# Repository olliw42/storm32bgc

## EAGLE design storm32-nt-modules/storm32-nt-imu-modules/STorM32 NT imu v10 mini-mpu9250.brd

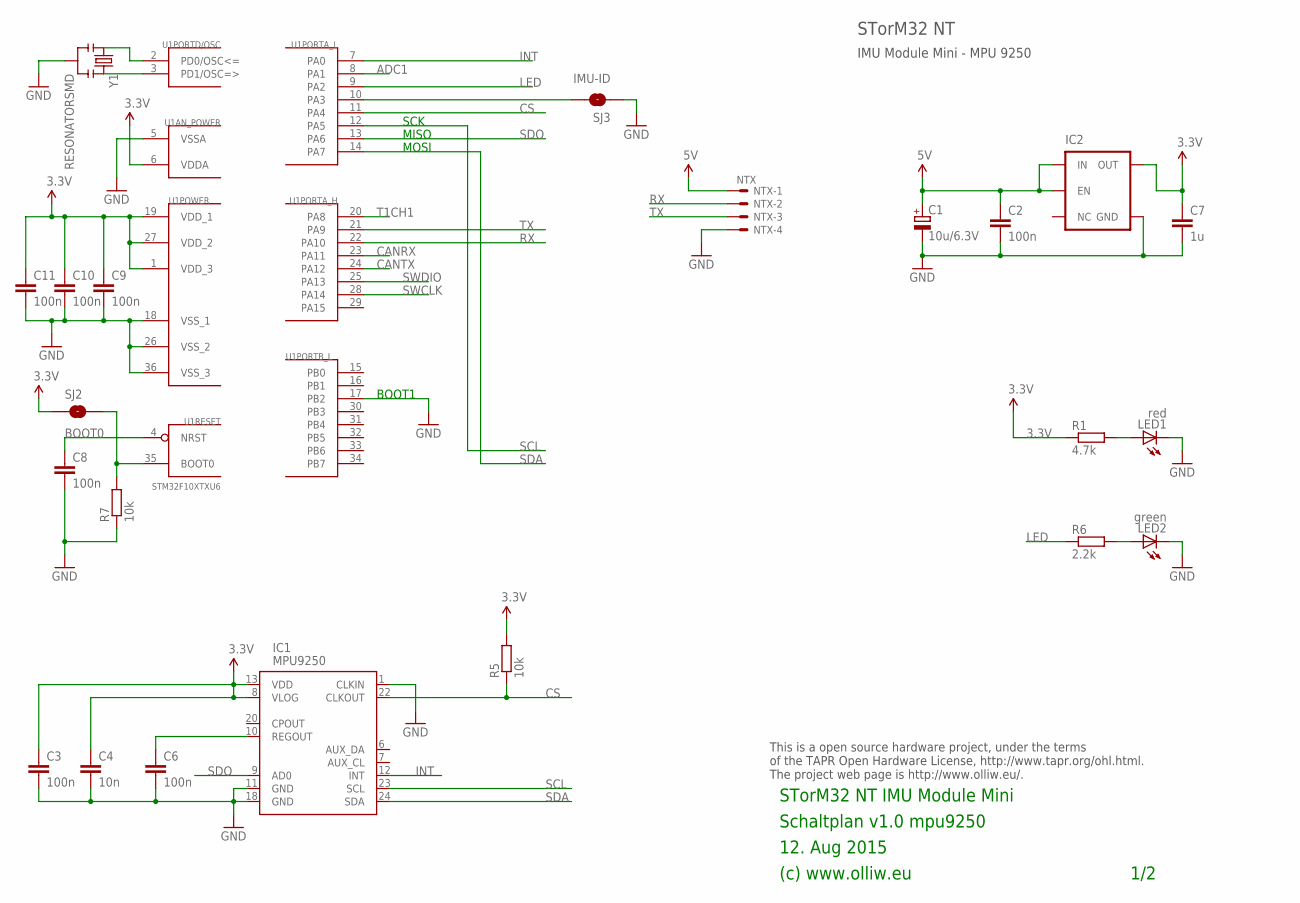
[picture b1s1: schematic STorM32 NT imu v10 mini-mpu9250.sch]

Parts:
C1: 10u/6.3V; SMC_A
C2, C3, C6, C8, C9, C10, C11: 100n; C0402
C4: 10n; C0402
C7: 1u; C0402
IC1: MPU9250; QFN-24-3X3
IC2: V_REG_TPS76433SOT23-5; SOT23-5
LED1: red; CHIPLED_0603
LED2: green; CHIPLED_0603
NTX: NTX; SM04B-SRSS-TB
R1: 4.7k; R0402
R5, R7: 10k; R0402
R6: 2.2k; R0402
SJ2: BOOT0; SJ_2S-NO
SJ3: IMU-ID; SJ_2S-NO
U1: STM32F10XTXU6; VFQFPN36
Y1: RESONATORSMD; RESONATOR-SMD

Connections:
3.3V: C3.1, C4.1, C7.1, C9.1, C10.1, C11.1, IC1.8 (VLOG), IC1.13 (VDD), IC2.5 (OUT), R1.1, R5.2, SJ2.1, U1.1 (VDD_3), U1.6 (VDDA), U1.19 (VDD_1), U1.27 (VDD_2)
5V: C1.+, C2.1, IC2.1 (IN), IC2.3 (EN), NTX.1
ADC1: U1.8 (PA1)
CANRX: U1.23 (PA11)
CANTX: U1.24 (PA12)
CS: IC1.22 (CLKOUT), R5.1, U1.11 (PA4)
GND: C1.-, C2.2, C3.2, C4.2, C6.2, C7.2, C8.2, C9.2, C10.2, C11.2, IC1.1 (CLKIN), IC1.11 (GND), IC1.18 (GND), IC2.2 (GND), LED1.C, LED2.C, NTX.4, R7.1, SJ3.1, U1.5 (VSSA), U1.17 (PB2), U1.18 (VSS_1), U1.26 (VSS_2), U1.36 (VSS_3), Y1.2
INT: IC1.12 (INT), U1.7 (PA0)
LED: R6.1, U1.9 (PA2)
unnamed: C8.1, U1.4 (NRST)
unnamed: LED2.A, R6.2
unnamed: R7.2, SJ2.2, U1.35 (BOOT0)
unnamed: U1.2 (PD0/OSC<=), Y1.1
unnamed: U1.3 (PD1/OSC=>), Y1.3
unnamed: LED1.A, R1.2
unnamed: C6.1, IC1.10 (REGOUT)
RX: NTX.2, U1.22 (PA10)
RX2: SJ3.2, U1.10 (PA3)
SCL: IC1.23 (SCL), U1.12 (PA5)
SDA: IC1.24 (SDA), U1.14 (PA7)
SDO: IC1.9 (AD0), U1.13 (PA6)
SWCLK: U1.28 (PA14)
SWDIO: U1.25 (PA13)
T1CH1: U1.20 (PA8)
TX: NTX.3, U1.21 (PA9)

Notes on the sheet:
12. Aug 2015
(c) www.olliw.eu
STorM32 NT IMU Module Mini
Schaltplan v1.0 mpu9250
This is a open source hardware project, under the terms of the TAPR Open Hardware License, http://www.tapr.org/ohl.html. The project web page is http://www.olliw.eu/.
1/2
IMU Module Mini - MPU 9250
STorM32 NT
SCK
MISO
MOSI
BOOT1

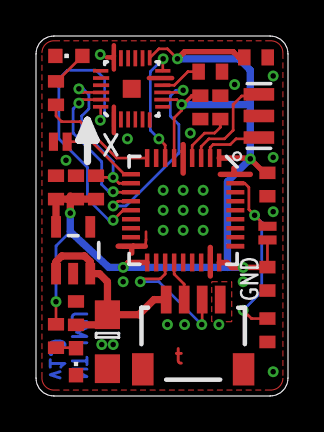
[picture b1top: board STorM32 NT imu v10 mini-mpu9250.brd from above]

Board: 2 copper layers, 14.0 x 20.0 mm, 23 parts (0 on the bottom side), 19 nets.

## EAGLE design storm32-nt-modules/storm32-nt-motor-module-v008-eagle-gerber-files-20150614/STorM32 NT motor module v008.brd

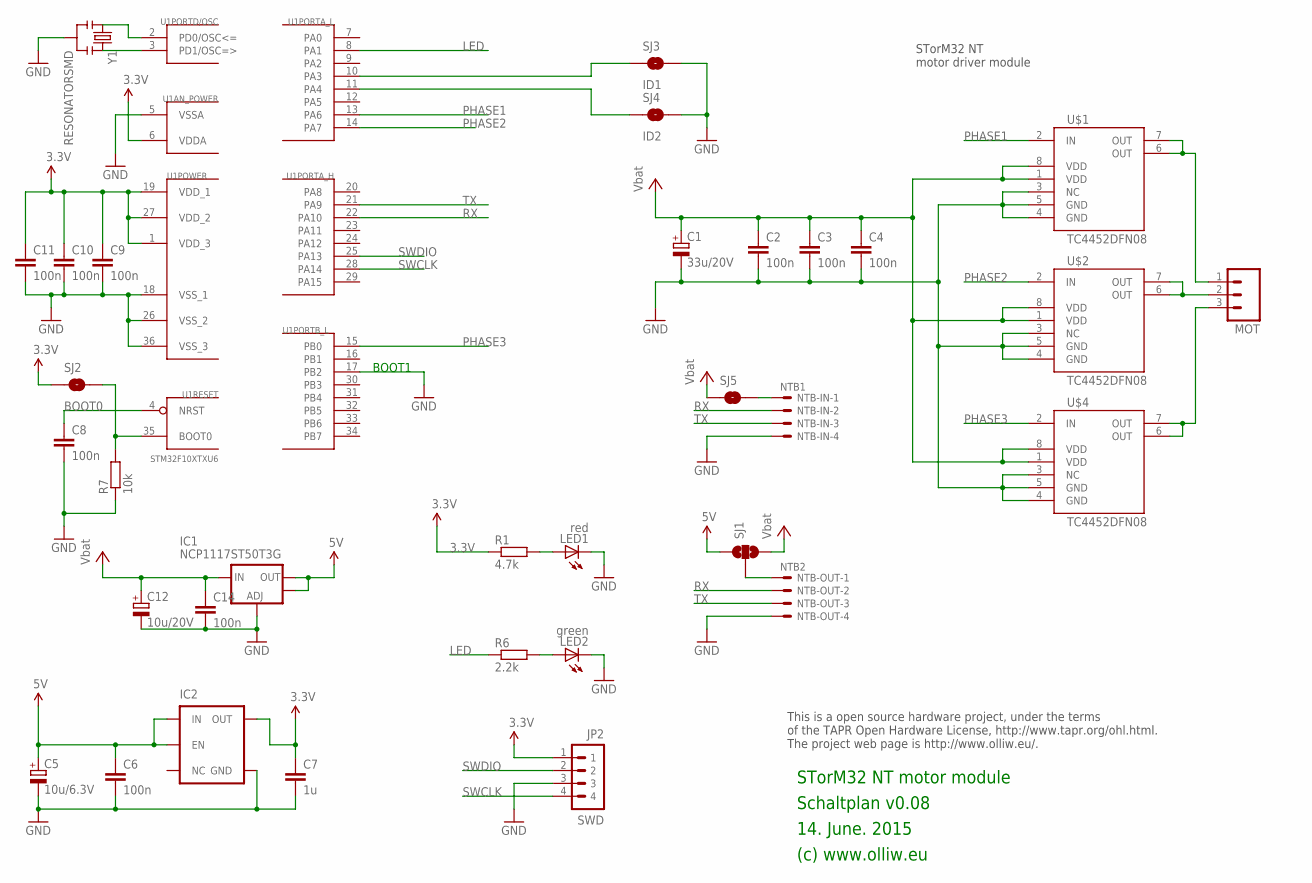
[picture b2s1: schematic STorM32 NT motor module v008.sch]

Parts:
C1: 33u/20V; SMC_C
C2, C3, C4, C6, C8, C9, C10, C11, C14: 100n; C0603
C5: 10u/6.3V; SMC_B
C7: 1u; C0603
C12: 10u/20V; SMC_B
IC1: NCP1117ST50T3G; SOT223
IC2: V_REG_TPS76433SOT23-5; SOT23-5
JP2: SWD; 4X1_1P27_OCT_BILEX
LED1: red; CHIPLED_0603
LED2: green; CHIPLED_0603
MOT: 1X03
NTB-IN: NTB1; SM04B-SRSS-TB
NTB-OUT: NTB2; SM04B-SRSS-TB
R1: 4.7k; R0603
R6: 2.2k; R0603
R7: 10k; R0603
SJ1: SOLDERJUMPER_2WAYT; SJ_2
SJ2: BOOT0; SJ_2S-NO
SJ3: ID1; SJ_2S-NO
SJ4: ID2; SJ_2S-NO
SJ5: SOLDERJUMPER; SJ_1T
U1: STM32F10XTXU6; VFQFPN36
U$1, U$2, U$4: TC4452DFN08; DFN8
Y1: RESONATORSMD; RESONATOR-SMD

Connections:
3.3V: C7.1, C9.1, C10.1, C11.1, IC2.5 (OUT), JP2.1, R1.1, SJ2.1, U1.1 (VDD_3), U1.6 (VDDA), U1.19 (VDD_1), U1.27 (VDD_2)
5V: C5.+, C6.1, IC1.2 (OUT), IC1.4 (OUT), IC2.1 (IN), IC2.3 (EN), SJ1.1
GND: C1.-, C2.2, C3.2, C4.2, C5.-, C6.2, C7.2, C8.2, C9.2, C10.2, C11.2, C12.-, C14.2, IC1.1 (ADJ), IC2.2 (GND), JP2.3, LED1.C, LED2.C, NTB-IN.4, NTB-OUT.4, R7.1, SJ3.2, SJ4.2, U1.5 (VSSA), U1.17 (PB2), U1.18 (VSS_1), U1.26 (VSS_2), U1.36 (VSS_3), U$1.3 (NC), U$1.4 (GND), U$1.5 (GND), U$2.3 (NC), U$2.4 (GND), U$2.5 (GND), U$4.3 (NC), U$4.4 (GND), U$4.5 (GND), Y1.2
LED: R6.1, U1.8 (PA1)
unnamed: MOT.2, U$2.6 (OUT), U$2.7 (OUT)
unnamed: NTB-OUT.1, SJ1.2
unnamed: SJ3.1, U1.10 (PA3)
unnamed: SJ4.1, U1.11 (PA4)
unnamed: MOT.1, U$1.6 (OUT), U$1.7 (OUT)
unnamed: MOT.3, U$4.6 (OUT), U$4.7 (OUT)
unnamed: C8.1, U1.4 (NRST)
unnamed: R7.2, SJ2.2, U1.35 (BOOT0)
unnamed: U1.2 (PD0/OSC<=), Y1.1
unnamed: U1.3 (PD1/OSC=>), Y1.3
unnamed: LED1.A, R1.2
unnamed: LED2.A, R6.2
unnamed: NTB-IN.1, SJ5.3 (2)
PHASE1: U1.13 (PA6), U$1.2 (IN)
PHASE2: U1.14 (PA7), U$2.2 (IN)
PHASE3: U1.15 (PB0), U$4.2 (IN)
RX: NTB-IN.2, NTB-OUT.2, U1.22 (PA10)
SWCLK: JP2.4, U1.28 (PA14)
SWDIO: JP2.2, U1.25 (PA13)
TX: NTB-IN.3, NTB-OUT.3, U1.21 (PA9)
VBAT: C1.+, C2.1, C3.1, C4.1, C12.+, C14.1, IC1.3 (IN), SJ1.3, SJ5.1, U$1.1 (VDD), U$1.8 (VDD), U$2.1 (VDD), U$2.8 (VDD), U$4.1 (VDD), U$4.8 (VDD)

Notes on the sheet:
14. June. 2015
(c) www.olliw.eu
STorM32 NT motor module
Schaltplan v0.08
This is a open source hardware project, under the terms of the TAPR Open Hardware License, http://www.tapr.org/ohl.html. The project web page is http://www.olliw.eu/.
STorM32 NT motor driver module
BOOT1

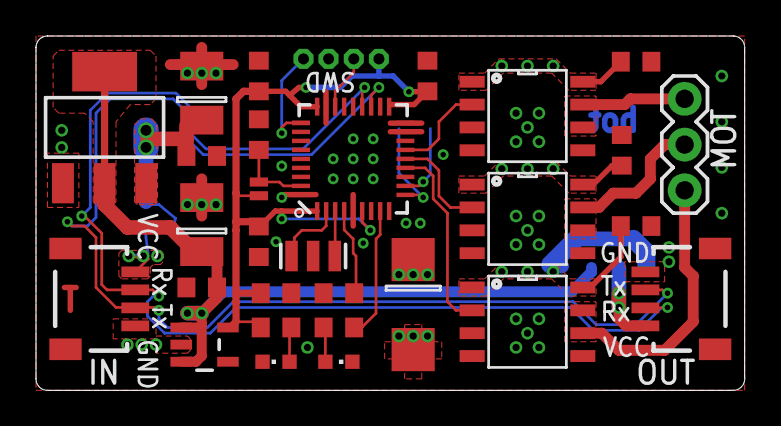
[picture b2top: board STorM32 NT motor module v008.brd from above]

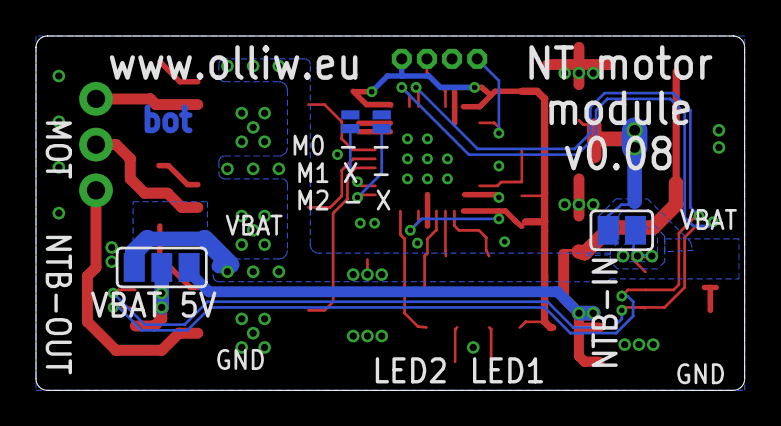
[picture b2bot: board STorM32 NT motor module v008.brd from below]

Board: 2 copper layers, 39.4 x 19.7 mm, 34 parts (4 on the bottom side), 25 nets.

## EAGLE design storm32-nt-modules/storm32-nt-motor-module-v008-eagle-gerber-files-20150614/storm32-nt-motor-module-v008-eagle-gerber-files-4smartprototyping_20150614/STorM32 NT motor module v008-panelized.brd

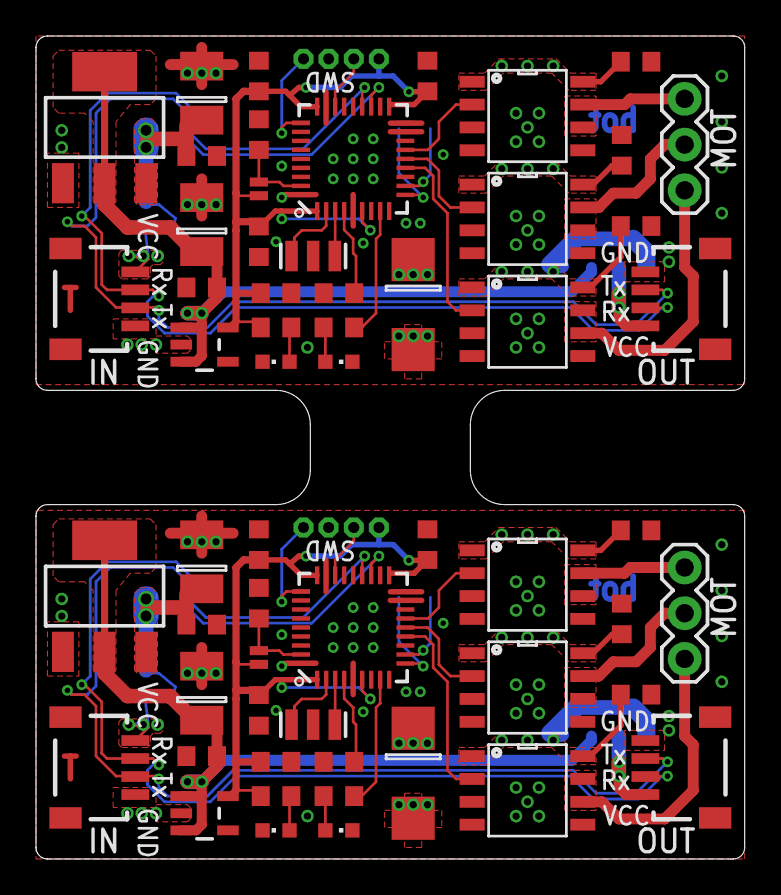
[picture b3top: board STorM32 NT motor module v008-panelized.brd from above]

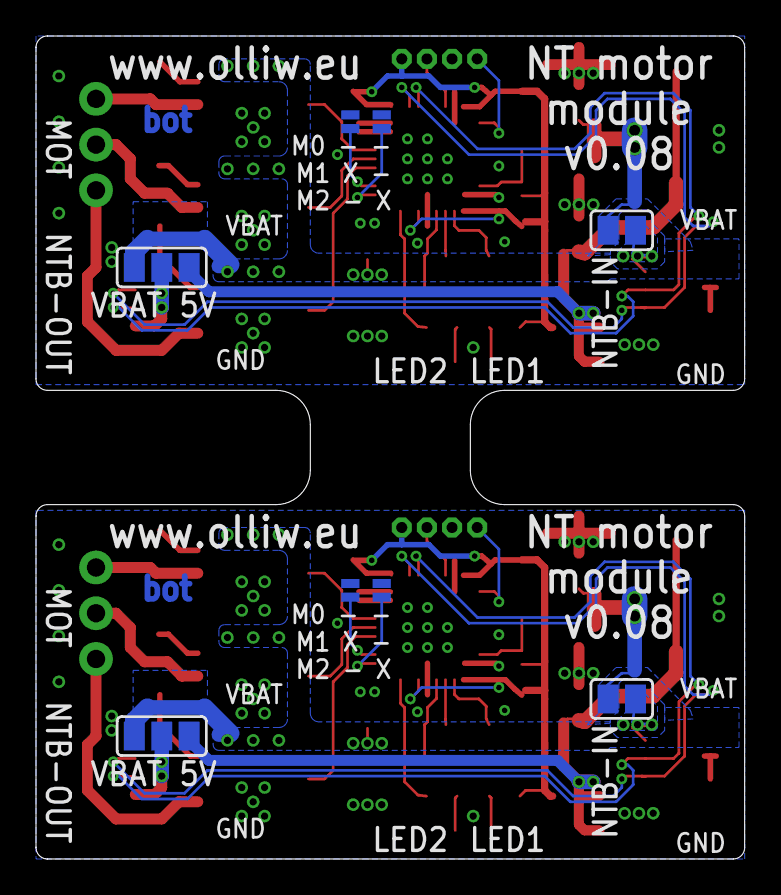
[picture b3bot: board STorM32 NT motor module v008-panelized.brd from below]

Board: 2 copper layers, 39.4 x 45.7 mm, 68 parts (8 on the bottom side), 50 nets.

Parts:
C1, C13: 33u/20V; SMC_C
C2, C3, C4, C6, C8, C9, C10, C11, C14, C15, C16, C17, C18, C19, C20, C21, C23, C26: 100n; C0603
C5, C22: 10u/6.3V; SMC_B
C7, C24: 1u; C0603
C12, C25: 10u/20V; SMC_B
IC1, IC4: NCP1117ST50T3G; SOT223
IC2, IC3: SOT23-5
JP1, JP2: SWD; 4X1_1P27_OCT_BILEX
LED1, LED3: red; CHIPLED_0603
LED2, LED4: green; CHIPLED_0603
MOT, MOT1: 1X03
NTB-IN, NTB-IN1: NTB1; SM04B-SRSS-TB
NTB-OUT, NTB-OUT1: NTB2; SM04B-SRSS-TB
R1, R3: 4.7k; R0603
R2, R7: 10k; R0603
R4, R6: 2.2k; R0603
SJ1, SJ7: SJ_2
SJ2, SJ6: BOOT0; SJ_2S-NO
SJ3, SJ8: ID1; SJ_2S-NO
SJ4, SJ9: ID2; SJ_2S-NO
SJ5, SJ10: SJ_1T
U1, U2: STM32F10XTXU6; VFQFPN36
U$1, U$2, U$3, U$4, U$5, U$6: TC4452DFN08; DFN8
Y1, Y2: RESONATORSMD; RESONATOR-SMD

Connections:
3.3V: C7.1, C9.1, C10.1, C11.1, IC2.5, JP2.1, R1.1, SJ2.1, U1.1, U1.6, U1.19, U1.27
3.3V1: C19.1, C20.1, C21.1, C24.1, IC3.5, JP1.1, R3.1, SJ6.1, U2.1, U2.6, U2.19, U2.27
5V: C5.+, C6.1, IC1.2, IC1.4, IC2.1, IC2.3, SJ1.1
5V1: C22.+, C23.1, IC3.1, IC3.3, IC4.2, IC4.4, SJ7.1
GND: C1.-, C2.2, C3.2, C4.2, C5.-, C6.2, C7.2, C8.2, C9.2, C10.2, C11.2, C12.-, C14.2, IC1.1, IC2.2, JP2.3, LED1.C, LED2.C, NTB-IN.4, NTB-OUT.4, R7.1, SJ3.2, SJ4.2, U1.5, U1.17, U1.18, U1.26, U1.36, U$1.3, U$1.4, U$1.5, U$2.3, U$2.4, U$2.5, U$4.3, U$4.4, U$4.5, Y1.2
GND1: C13.-, C15.2, C16.2, C17.2, C18.2, C19.2, C20.2, C21.2, C22.-, C23.2, C24.2, C25.-, C26.2, IC3.2, IC4.1, JP1.3, LED3.C, LED4.C, NTB-IN1.4, NTB-OUT1.4, R2.1, SJ8.2, SJ9.2, U2.5, U2.17, U2.18, U2.26, U2.36, U$3.3, U$3.4, U$3.5, U$5.3, U$5.4, U$5.5, U$6.3, U$6.4, U$6.5, Y2.2
LED: R6.1, U1.8
LED1: R4.1, U2.8
unnamed: MOT.2, U$2.6, U$2.7
unnamed: NTB-OUT.1, SJ1.2
unnamed: SJ3.1, U1.10
unnamed: SJ4.1, U1.11
unnamed: MOT.1, U$1.6, U$1.7
unnamed: MOT.3, U$4.6, U$4.7
unnamed: C8.1, U1.4
unnamed: R7.2, SJ2.2, U1.35
unnamed: U1.2, Y1.1
unnamed: U1.3, Y1.3
unnamed: LED1.A, R1.2
unnamed: LED2.A, R6.2
unnamed: NTB-IN.1, SJ5.3
unnamed: MOT1.2, U$5.6, U$5.7
unnamed: MOT1.1, U$3.6, U$3.7
unnamed: MOT1.3, U$6.6, U$6.7
unnamed: C18.1, U2.4
unnamed: R2.2, SJ6.2, U2.35
unnamed: U2.2, Y2.1
unnamed: U2.3, Y2.3
unnamed: LED3.A, R3.2
unnamed: LED4.A, R4.2
unnamed: NTB-OUT1.1, SJ7.2
unnamed: SJ8.1, U2.10
unnamed: SJ9.1, U2.11
unnamed: NTB-IN1.1, SJ10.3
PHASE1: U1.13, U$1.2
PHASE2: U1.14, U$2.2
PHASE3: U1.15, U$4.2
PHASE4: U2.13, U$3.2
PHASE5: U2.15, U$6.2
PHASE6: U2.14, U$5.2
RX: NTB-IN.2, NTB-OUT.2, U1.22
RX1: NTB-IN1.2, NTB-OUT1.2, U2.22
SWCLK: JP2.4, U1.28
SWCLK1: JP1.4, U2.28
SWDIO: JP2.2, U1.25
SWDIO1: JP1.2, U2.25
TX: NTB-IN.3, NTB-OUT.3, U1.21
TX1: NTB-IN1.3, NTB-OUT1.3, U2.21
VBAT: C1.+, C2.1, C3.1, C4.1, C12.+, C14.1, IC1.3, SJ1.3, SJ5.1, U$1.1, U$1.8, U$2.1, U$2.8, U$4.1, U$4.8
VBAT1: C13.+, C15.1, C16.1, C17.1, C25.+, C26.1, IC4.3, SJ7.3, SJ10.1, U$3.1, U$3.8, U$5.1, U$5.8, U$6.1, U$6.8

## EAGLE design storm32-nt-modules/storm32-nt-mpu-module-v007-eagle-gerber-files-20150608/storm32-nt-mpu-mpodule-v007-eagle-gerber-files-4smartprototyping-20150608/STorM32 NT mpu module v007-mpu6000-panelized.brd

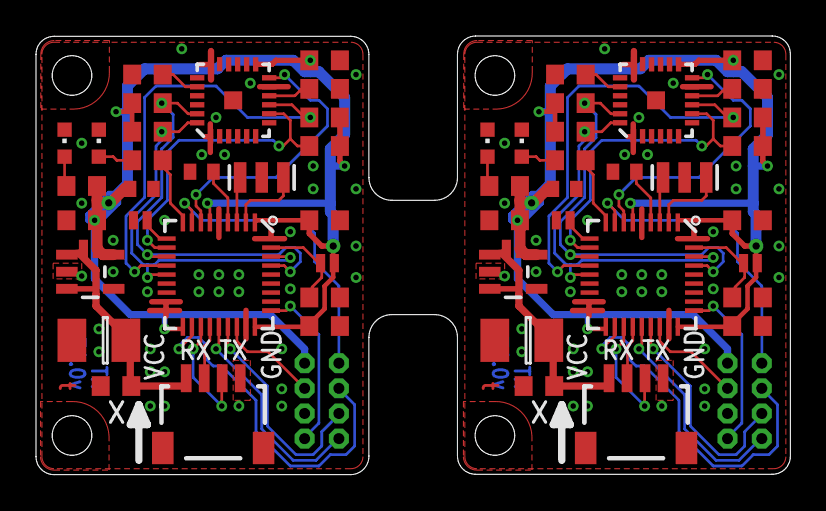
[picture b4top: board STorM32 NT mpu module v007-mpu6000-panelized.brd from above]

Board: 2 copper layers, 41.9 x 24.4 mm, 58 parts (0 on the bottom side), 52 nets.

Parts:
C1, C4: 10u/6.3V; SMC_B
C2, C3, C6, C9, C11, C12, C14, C15, C18, C20: 100n; C0603
C5, C13: 2.2n; C0603
C7, C16: 1u; C0603
C8, C10, C17, C19: 100n; C0402
IC1, IC3: MPU6000; QFN-24
IC2, IC4: SOT23-5
JP1, JP3: EXT; 4X1_1P27_OCT_BILEX
JP2, JP4: SWD; 4X1_1P27_OCT_BILEX
LED1, LED3: red; CHIPLED_0603
LED2, LED4: green; CHIPLED_0603
NTX, NTX1: NTX; SM04B-SRSS-TB
R1, R2, R3, R6, R8, R9, R10, R14: 2.2k; R0603
R4, R5, R7, R11, R12, R13: 10k; R0603
SJ1, SJ4: POWER; SJ_2S-NO
SJ2, SJ5: BOOT0; SJ_2S-NO
SJ3, SJ6: IMU-ID; SJ_2S-NO
U1, U2: STM32F10XTXU6; VFQFPN36
Y1, Y2: RESONATORSMD; RESONATOR-SMD

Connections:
3.3V: C3.1, C7.1, C9.1, C10.1, C11.1, IC1.13, IC2.5, JP2.1, R1.1, R2.2, R3.2, R4.2, R5.2, SJ1.2, SJ2.1, U1.1, U1.6, U1.19, U1.27
3.3V1: C14.1, C16.1, C18.1, C19.1, C20.1, IC3.13, IC4.5, JP4.1, R8.2, R9.2, R10.1, R11.2, R12.2, SJ4.2, SJ5.1, U2.1, U2.6, U2.19, U2.27
5V2: C1.+, C2.1, IC2.1, IC2.3, NTX.1, SJ1.1
5V3: C4.+, C15.1, IC4.1, IC4.3, NTX1.1, SJ4.1
ADC3: JP1.1, U1.8
ADC4: JP3.1, U2.8
CANRX2: JP1.4, U1.23
CANRX3: JP3.4, U2.23
CANTX2: JP1.3, U1.24
CANTX3: JP3.3, U2.24
CS2: IC1.8, R5.1, U1.11
CS3: IC3.8, R12.1, U2.11
GND: C1.-, C2.2, C3.2, C5.2, C6.2, C7.2, C8.2, C9.2, C10.2, C11.2, IC1.1, IC1.11, IC1.18, IC2.2, JP2.3, LED1.C, LED2.C, NTX.4, R7.1, SJ3.1, U1.5, U1.17, U1.18, U1.26, U1.36, Y1.2
GND5: C4.-, C12.2, C13.2, C14.2, C15.2, C16.2, C17.2, C18.2, C19.2, C20.2, IC3.1, IC3.11, IC3.18, IC4.2, JP4.3, LED3.C, LED4.C, NTX1.4, R13.1, SJ6.1, U2.5, U2.17, U2.18, U2.26, U2.36, Y2.2
INT2: IC1.12, U1.7
INT3: IC3.12, U2.7
LED2: R6.1, U1.9
LED3: R14.1, U2.9
unnamed: LED1.A, R1.2
unnamed: C6.1, IC1.10
unnamed: C5.1, IC1.20
unnamed: C8.1, U1.4
unnamed: R7.2, SJ2.2, U1.35
unnamed: LED2.A, R6.2
unnamed: U1.2, Y1.1
unnamed: U1.3, Y1.3
unnamed: LED3.A, R10.2
unnamed: C12.1, IC3.10
unnamed: C13.1, IC3.20
unnamed: C17.1, U2.4
unnamed: R13.2, SJ5.2, U2.35
unnamed: LED4.A, R14.2
unnamed: U2.2, Y2.1
unnamed: U2.3, Y2.3
RX3: NTX.2, U1.22
RX4: SJ3.2, U1.10
RX5: NTX1.2, U2.22
RX6: SJ6.2, U2.10
SCL2: IC1.23, R2.1, U1.12, U1.33
SCL3: IC3.23, R8.1, U2.12, U2.33
SDA2: IC1.24, R3.1, U1.14, U1.34
SDA3: IC3.24, R9.1, U2.14, U2.34
SDO2: IC1.9, R4.1, U1.13
SDO3: IC3.9, R11.1, U2.13
SWCLK1: JP2.4, U1.28
SWCLK2: JP4.4, U2.28
SWDIO2: JP2.2, U1.25
SWDIO3: JP4.2, U2.25
T1CH2: JP1.2, U1.20
T1CH3: JP3.2, U2.20
TX2: NTX.3, U1.21
TX3: NTX1.3, U2.21

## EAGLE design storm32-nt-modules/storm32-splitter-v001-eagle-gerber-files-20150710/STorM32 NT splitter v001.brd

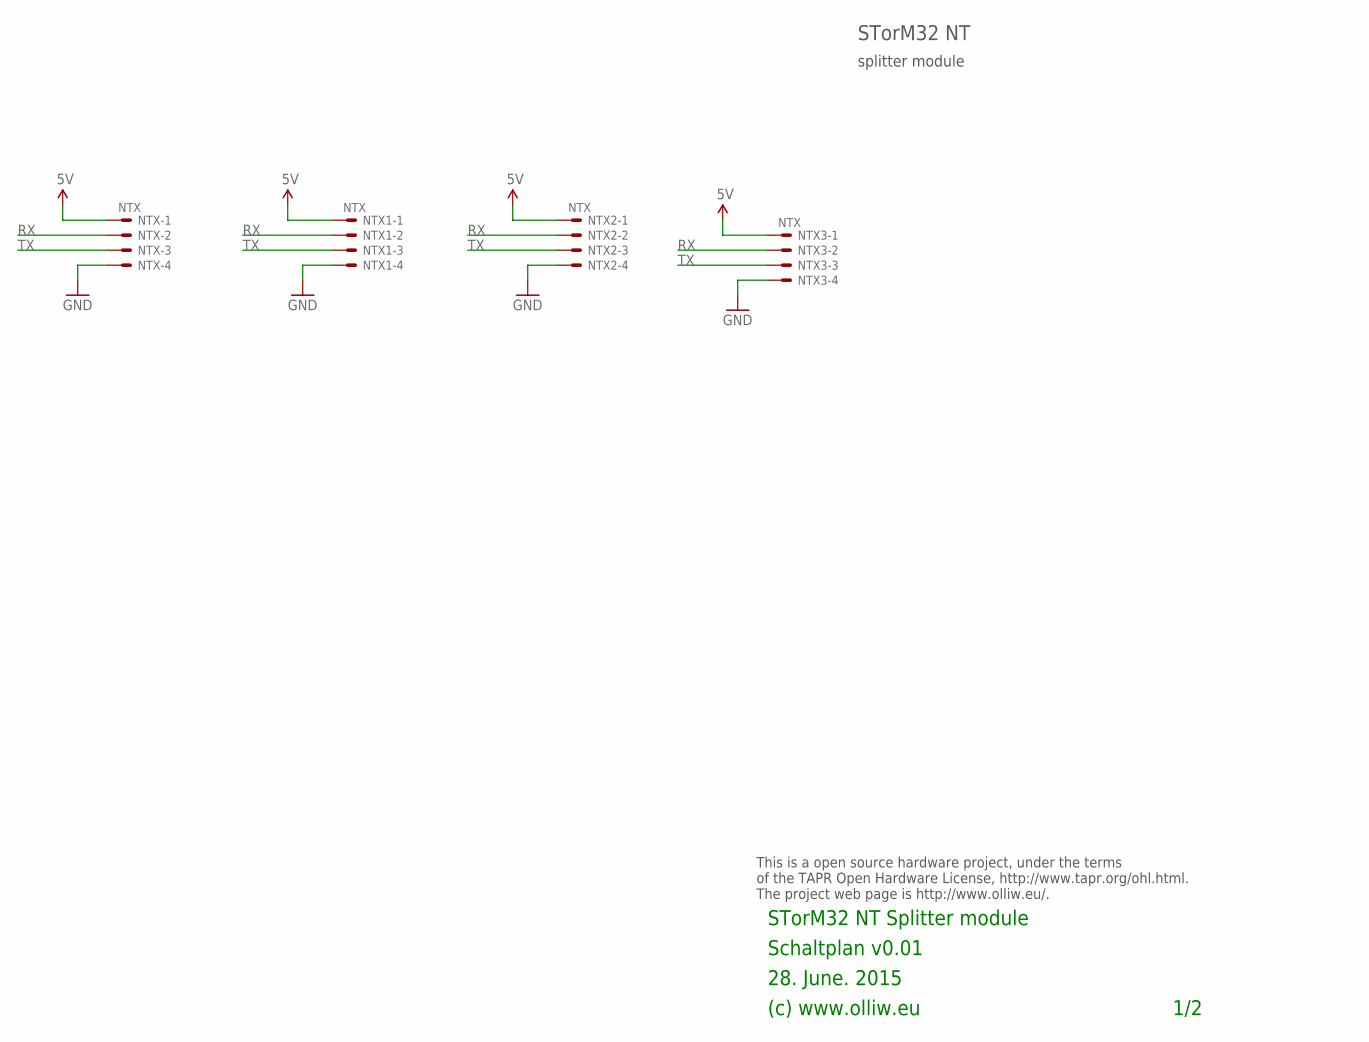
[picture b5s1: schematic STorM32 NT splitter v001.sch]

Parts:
NTX, NTX1, NTX2, NTX3: NTX; SM04B-SRSS-TB

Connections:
5V: NTX.1, NTX1.1, NTX2.1, NTX3.1
GND: NTX.4, NTX1.4, NTX2.4, NTX3.4
RX: NTX.2, NTX1.2, NTX2.2, NTX3.2
TX: NTX.3, NTX1.3, NTX2.3, NTX3.3

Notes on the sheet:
28. June. 2015
(c) www.olliw.eu
STorM32 NT Splitter module
Schaltplan v0.01
This is a open source hardware project, under the terms of the TAPR Open Hardware License, http://www.tapr.org/ohl.html. The project web page is http://www.olliw.eu/.
1/2
splitter module
STorM32 NT

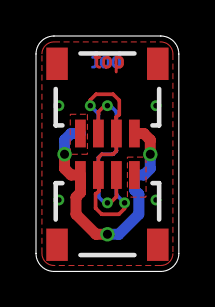
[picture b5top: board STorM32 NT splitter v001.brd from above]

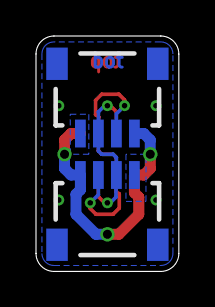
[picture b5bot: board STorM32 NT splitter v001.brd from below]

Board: 2 copper layers, 7.9 x 13.1 mm, 4 parts (2 on the bottom side), 4 nets.

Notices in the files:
parts and their libraries:
Licensing: CC v3.0 Share-Alike You are welcome to use this library for commercial purposes.
